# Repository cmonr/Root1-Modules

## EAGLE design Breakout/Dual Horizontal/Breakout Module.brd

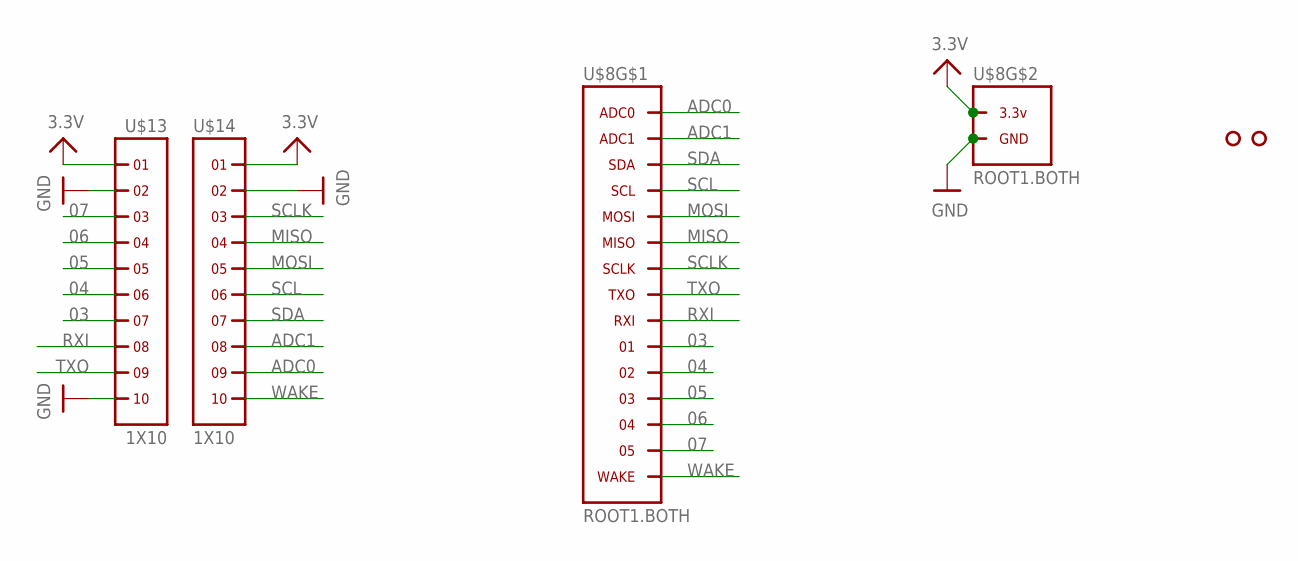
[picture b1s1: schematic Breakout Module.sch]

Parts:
U$3, U$4: HOLE.2MM; 2MM
U$8: ROOT1.BOTH
U$13, U$14: 1X10

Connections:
03: U$8.03 (01), U$8.03@1 (01), U$8.03@VIA (01), U$13.7
3.3V: U$8.3.3V@1 (3.3V), U$8.3.3V@2 (3.3V), U$8.3.3V@3 (3.3V), U$8.3.3V@4 (3.3V), U$8.3.3V@5 (3.3V), U$8.3.3V@6 (3.3V), U$8.3.3V@7 (3.3V), U$8.3.3V@8 (3.3V), U$8.3.3V@9 (3.3V), U$8.3.3V@10 (3.3V), U$8.3.3V@VIA (3.3V), U$13.1, U$14.1
04: U$8.04 (02), U$8.04@1 (02), U$8.04@VIA (02), U$13.6
05: U$8.05 (03), U$8.05@1 (03), U$8.05@VIA (03), U$13.5
06: U$8.06 (04), U$8.06@1 (04), U$8.06@VIA (04), U$13.4
07: U$8.07 (05), U$8.07@1 (05), U$8.07@VIA (05), U$13.3
ADC0: U$8.ADC0, U$8.ADC0@1 (ADC0), U$8.ADC0@VIA (ADC0), U$14.9
ADC1: U$8.ADC1, U$8.ADC1@1 (ADC1), U$8.ADC1@VIA (ADC1), U$14.8
GND: U$8.GND@1 (GND), U$8.GND@2 (GND), U$8.GND@3 (GND), U$8.GND@4 (GND), U$8.GND@5 (GND), U$8.GND@6 (GND), U$8.GND@7 (GND), U$8.GND@8 (GND), U$8.GND@9 (GND), U$8.GND@10 (GND), U$8.GND@11 (GND), U$8.GND@12 (GND), U$8.GND@13 (GND), U$8.GND@14 (GND), U$8.GND@15 (GND), U$8.GND@16 (GND), U$8.GND@17 (GND), U$8.GND@18 (GND), U$8.GND@19 (GND), U$8.GND@20 (GND), U$8.GND@VIA (GND), U$13.2, U$13.10, U$14.2
MISO: U$8.MISO, U$8.MISO@1 (MISO), U$8.MISO@VIA (MISO), U$14.4
MOSI: U$8.MOSI, U$8.MOSI@1 (MOSI), U$8.MOSI@VIA (MOSI), U$14.5
RXI: U$8.02 (RXI), U$8.02@1 (RXI), U$8.02@VIA (RXI), U$13.8
SCL: U$8.SCL, U$8.SCL@1 (SCL), U$8.SCL@VIA (SCL), U$14.6
SCLK: U$8.SCLK, U$8.SCLK@1 (SCLK), U$8.SCLK@VIA (SCLK), U$14.3
SDA: U$8.SDA, U$8.SDA@1 (SDA), U$8.SDA@VIA (SDA), U$14.7
TXO: U$8.01 (TXO), U$8.01@1 (TXO), U$8.01@VIA (TXO), U$13.9
WAKE: U$8.WAKE, U$8.WAKE@1 (WAKE), U$8.WAKE@VIA (WAKE), U$14.10

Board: 2 copper layers, 5 parts (0 on the bottom side), 17 nets, no tracks yet.

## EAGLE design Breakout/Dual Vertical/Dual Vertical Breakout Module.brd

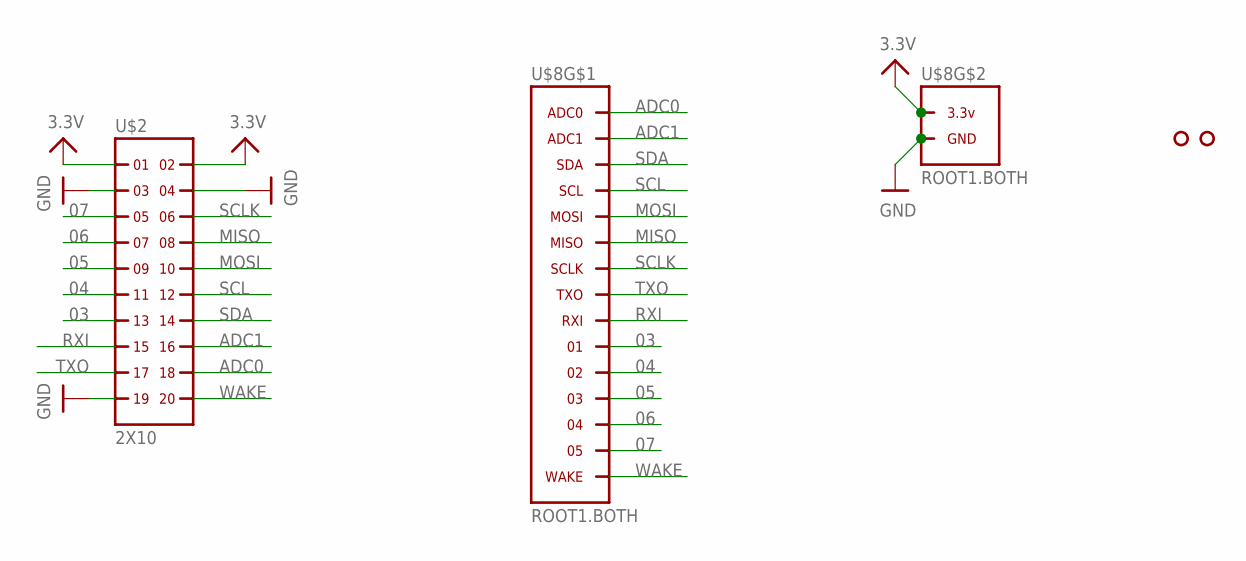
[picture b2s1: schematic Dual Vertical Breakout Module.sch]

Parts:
U$2: 2X10
U$3, U$4: HOLE.2MM; 2MM
U$8: ROOT1.BOTH

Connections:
03: U$2.13, U$8.03 (01), U$8.03@1 (01), U$8.03@VIA (01)
3.3V: U$2.1, U$2.2, U$8.3.3V@1 (3.3V), U$8.3.3V@2 (3.3V), U$8.3.3V@3 (3.3V), U$8.3.3V@4 (3.3V), U$8.3.3V@5 (3.3V), U$8.3.3V@6 (3.3V), U$8.3.3V@7 (3.3V), U$8.3.3V@8 (3.3V), U$8.3.3V@9 (3.3V), U$8.3.3V@10 (3.3V), U$8.3.3V@VIA (3.3V)
04: U$2.11, U$8.04 (02), U$8.04@1 (02), U$8.04@VIA (02)
05: U$2.9, U$8.05 (03), U$8.05@1 (03), U$8.05@VIA (03)
06: U$2.7, U$8.06 (04), U$8.06@1 (04), U$8.06@VIA (04)
07: U$2.5, U$8.07 (05), U$8.07@1 (05), U$8.07@VIA (05)
ADC0: U$2.18, U$8.ADC0, U$8.ADC0@1 (ADC0), U$8.ADC0@VIA (ADC0)
ADC1: U$2.16, U$8.ADC1, U$8.ADC1@1 (ADC1), U$8.ADC1@VIA (ADC1)
GND: U$2.3, U$2.4, U$2.19, U$8.GND@1 (GND), U$8.GND@2 (GND), U$8.GND@3 (GND), U$8.GND@4 (GND), U$8.GND@5 (GND), U$8.GND@6 (GND), U$8.GND@7 (GND), U$8.GND@8 (GND), U$8.GND@9 (GND), U$8.GND@10 (GND), U$8.GND@11 (GND), U$8.GND@12 (GND), U$8.GND@13 (GND), U$8.GND@14 (GND), U$8.GND@15 (GND), U$8.GND@16 (GND), U$8.GND@17 (GND), U$8.GND@18 (GND), U$8.GND@19 (GND), U$8.GND@20 (GND), U$8.GND@VIA (GND)
MISO: U$2.8, U$8.MISO, U$8.MISO@1 (MISO), U$8.MISO@VIA (MISO)
MOSI: U$2.10, U$8.MOSI, U$8.MOSI@1 (MOSI), U$8.MOSI@VIA (MOSI)
RXI: U$2.15, U$8.02 (RXI), U$8.02@1 (RXI), U$8.02@VIA (RXI)
SCL: U$2.12, U$8.SCL, U$8.SCL@1 (SCL), U$8.SCL@VIA (SCL)
SCLK: U$2.6, U$8.SCLK, U$8.SCLK@1 (SCLK), U$8.SCLK@VIA (SCLK)
SDA: U$2.14, U$8.SDA, U$8.SDA@1 (SDA), U$8.SDA@VIA (SDA)
TXO: U$2.17, U$8.01 (TXO), U$8.01@1 (TXO), U$8.01@VIA (TXO)
WAKE: U$2.20, U$8.WAKE, U$8.WAKE@1 (WAKE), U$8.WAKE@VIA (WAKE)

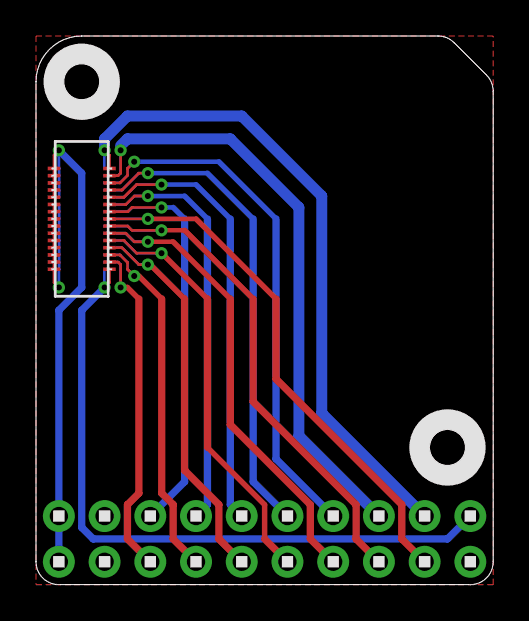
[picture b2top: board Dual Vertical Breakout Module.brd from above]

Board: 2 copper layers, 25.4 x 30.5 mm, 4 parts (0 on the bottom side), 17 nets.

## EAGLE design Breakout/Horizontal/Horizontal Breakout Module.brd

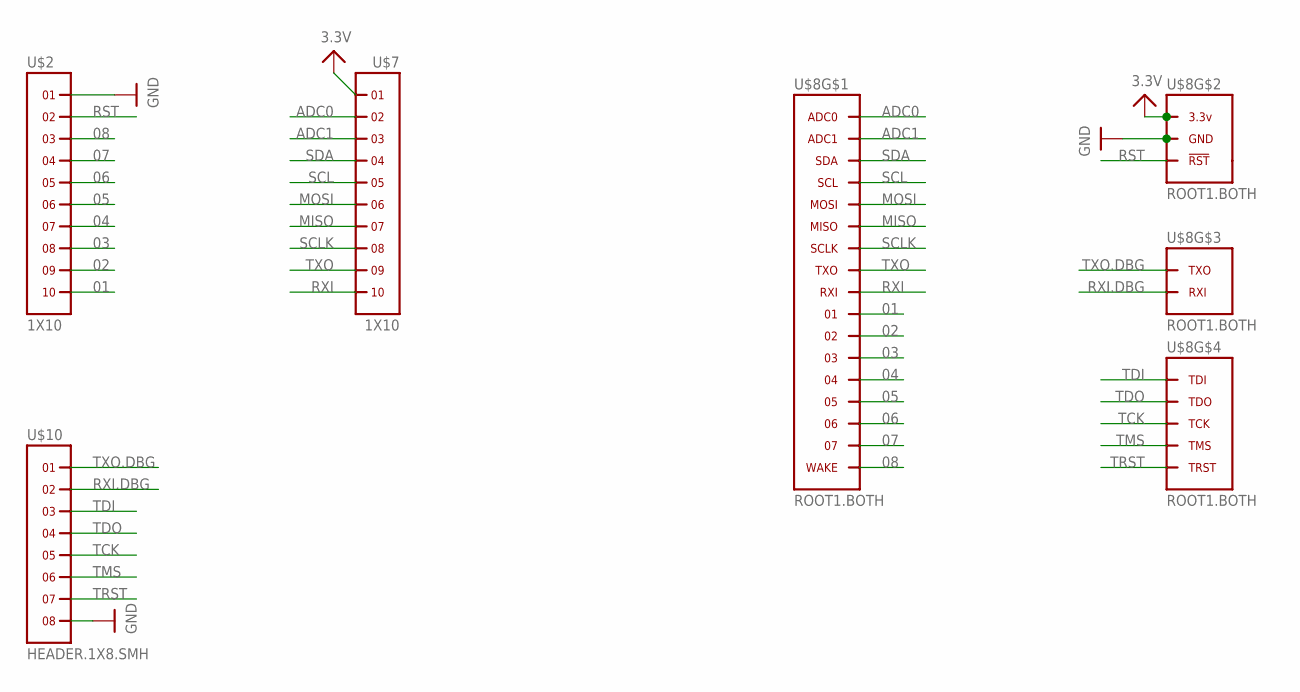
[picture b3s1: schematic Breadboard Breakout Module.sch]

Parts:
U$2, U$7: 1X10
U$8: ROOT1.BOTH
U$10: HEADER.1X8.SMH; SMH-108-XX-X-S

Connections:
01: U$2.10, U$8.01, U$8.01@1 (01), U$8.01@VIA (01)
02: U$2.9, U$8.02, U$8.02@1 (02), U$8.02@VIA (02)
03: U$2.8, U$8.03, U$8.03@1 (03), U$8.03@VIA (03)
3.3V: U$7.1, U$8.3.3V@1 (3.3V), U$8.3.3V@2 (3.3V), U$8.3.3V@3 (3.3V), U$8.3.3V@4 (3.3V), U$8.3.3V@5 (3.3V), U$8.3.3V@6 (3.3V), U$8.3.3V@7 (3.3V), U$8.3.3V@8 (3.3V), U$8.3.3V@9 (3.3V), U$8.3.3V@10 (3.3V), U$8.3.3V@11 (3.3V), U$8.3.3V@12 (3.3V), U$8.3.3V@13 (3.3V), U$8.3.3V@14 (3.3V), U$8.3.3V@15 (3.3V), U$8.3.3V@16 (3.3V), U$8.3.3V@17 (3.3V), U$8.3.3V@18 (3.3V), U$8.3.3V@19 (3.3V), U$8.3.3V@20 (3.3V), U$8.3.3V@21 (3.3V), U$8.3.3V@22 (3.3V), U$8.3.3V@23 (3.3V), U$8.3.3V@24 (3.3V), U$8.3.3V@VIA (3.3V)
04: U$2.7, U$8.04, U$8.04@1 (04), U$8.04@VIA (04)
05: U$2.6, U$8.05, U$8.05@1 (05), U$8.05@VIA (05)
06: U$2.5, U$8.06, U$8.06@1 (06), U$8.06@VIA (06)
07: U$2.4, U$8.07, U$8.07@1 (07), U$8.07@VIA (07)
08: U$2.3, U$8.WAKE, U$8.WAKE@1 (WAKE), U$8.WAKE@VIA (WAKE)
ADC0: U$7.2, U$8.ADC0, U$8.ADC0@1 (ADC0), U$8.ADC0@VIA (ADC0)
ADC1: U$7.3, U$8.ADC1, U$8.ADC1@1 (ADC1), U$8.ADC1@VIA (ADC1)
GND: U$2.1, U$8.GND@1 (GND), U$8.GND@2 (GND), U$8.GND@3 (GND), U$8.GND@4 (GND), U$8.GND@5 (GND), U$8.GND@6 (GND), U$8.GND@7 (GND), U$8.GND@8 (GND), U$8.GND@9 (GND), U$8.GND@10 (GND), U$8.GND@11 (GND), U$8.GND@12 (GND), U$8.GND@13 (GND), U$8.GND@14 (GND), U$8.GND@15 (GND), U$8.GND@16 (GND), U$8.GND@17 (GND), U$8.GND@18 (GND), U$8.GND@19 (GND), U$8.GND@20 (GND), U$8.GND@21 (GND), U$8.GND@22 (GND), U$8.GND@23 (GND), U$8.GND@24 (GND), U$8.GND@25 (GND), U$8.GND@26 (GND), U$8.GND@VIA (GND), U$10.8
MISO: U$7.7, U$8.MISO, U$8.MISO@1 (MISO), U$8.MISO@VIA (MISO)
MOSI: U$7.6, U$8.MOSI, U$8.MOSI@1 (MOSI), U$8.MOSI@VIA (MOSI)
RST: U$2.2, U$8.RST (!RST), U$8.RST@1 (!RST), U$8.RST@VIA (!RST)
RXI: U$7.10, U$8.RXI, U$8.RXI@1 (RXI), U$8.RXI@VIA (RXI)
RXI.DBG: U$8.RXI.DBG (RXI), U$8.RXI.DBG@1 (RXI), U$8.RXI.DBG@VIA (RXI), U$10.2
SCL: U$7.5, U$8.SCL, U$8.SCL@1 (SCL), U$8.SCL@VIA (SCL)
SCLK: U$7.8, U$8.SCLK, U$8.SCLK@1 (SCLK), U$8.SCLK@VIA (SCLK)
SDA: U$7.4, U$8.SDA, U$8.SDA@1 (SDA), U$8.SDA@VIA (SDA)
TCK: U$8.TCK, U$8.TCK@1 (TCK), U$8.TCK@VIA (TCK), U$10.5
TDI: U$8.TDI, U$8.TDI@1 (TDI), U$8.TDI@VIA (TDI), U$10.3
TDO: U$8.TDO, U$8.TDO@1 (TDO), U$8.TDO@VIA (TDO), U$10.4
TMS: U$8.TMS, U$8.TMS@1 (TMS), U$8.TMS@VIA (TMS), U$10.6
TRST: U$8.TRST, U$8.TRST@1 (TRST), U$8.TRST@VIA (TRST), U$10.7
TXO: U$7.9, U$8.TXO, U$8.TXO@1 (TXO), U$8.TXO@VIA (TXO)
TXO.DBG: U$8.TXO.DBG (TXO), U$8.TXO.DBG@1 (TXO), U$8.TXO.DBG@VIA (TXO), U$10.1

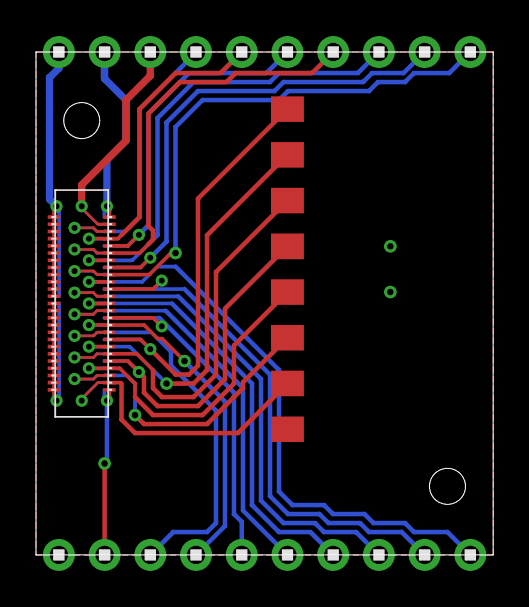
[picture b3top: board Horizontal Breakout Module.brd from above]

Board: 2 copper layers, 25.4 x 27.9 mm, 4 parts (0 on the bottom side), 27 nets.

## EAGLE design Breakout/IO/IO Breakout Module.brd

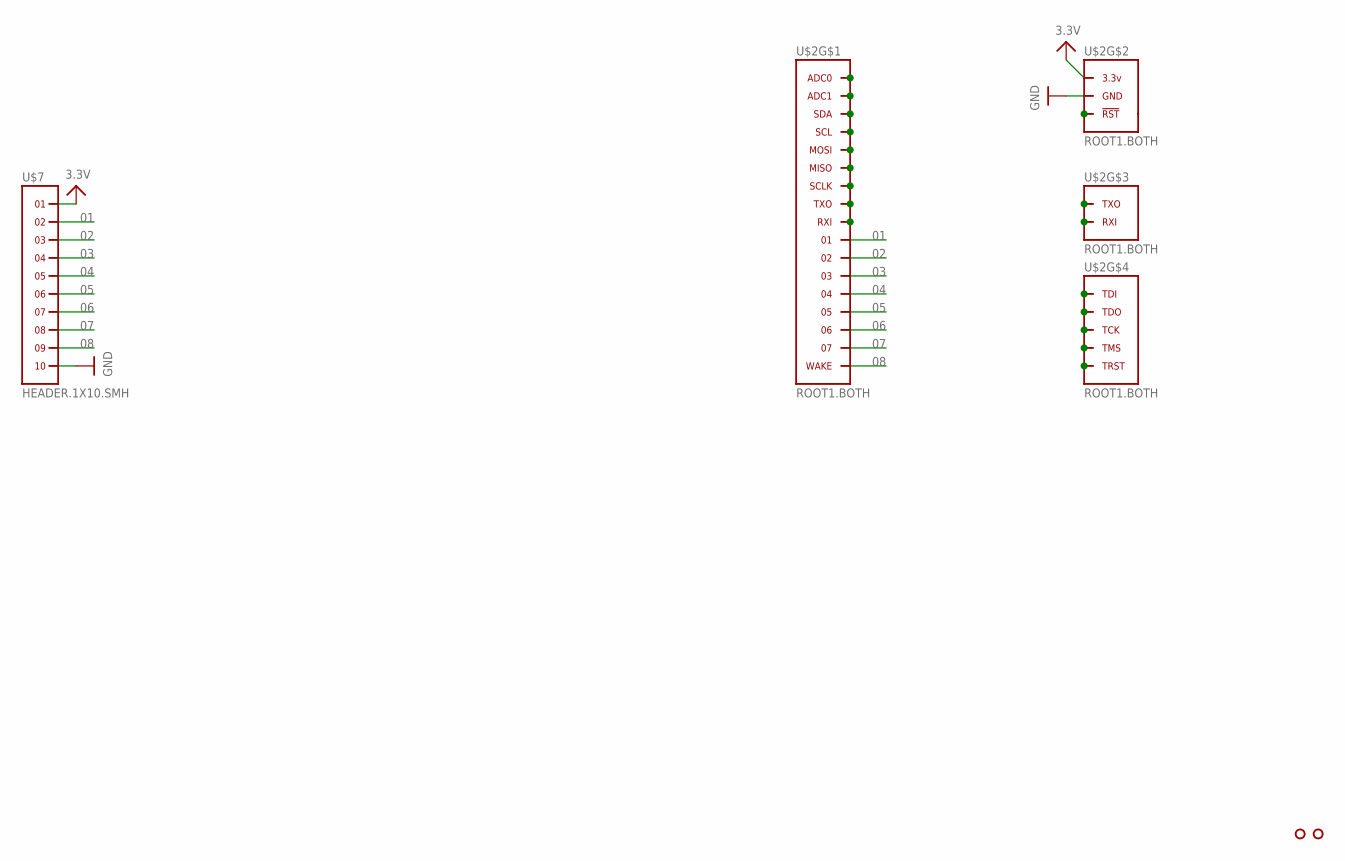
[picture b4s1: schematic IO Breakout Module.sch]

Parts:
U$2: ROOT1.BOTH
U$3, U$4: HOLE.#2; #2
U$7: HEADER.1X10.SMH; SMH-110-XX-X-S

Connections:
01: U$2.01, U$2.01@1 (01), U$2.01@VIA (01), U$7.2
02: U$2.02, U$2.02@1 (02), U$2.02@VIA (02), U$7.3
03: U$2.03, U$2.03@1 (03), U$2.03@VIA (03), U$7.4
3.3V: U$2.3.3V@1 (3.3V), U$2.3.3V@2 (3.3V), U$2.3.3V@3 (3.3V), U$2.3.3V@4 (3.3V), U$2.3.3V@5 (3.3V), U$2.3.3V@6 (3.3V), U$2.3.3V@7 (3.3V), U$2.3.3V@8 (3.3V), U$2.3.3V@9 (3.3V), U$2.3.3V@10 (3.3V), U$2.3.3V@11 (3.3V), U$2.3.3V@12 (3.3V), U$2.3.3V@13 (3.3V), U$2.3.3V@14 (3.3V), U$2.3.3V@15 (3.3V), U$2.3.3V@16 (3.3V), U$2.3.3V@17 (3.3V), U$2.3.3V@18 (3.3V), U$2.3.3V@19 (3.3V), U$2.3.3V@20 (3.3V), U$2.3.3V@21 (3.3V), U$2.3.3V@22 (3.3V), U$2.3.3V@23 (3.3V), U$2.3.3V@24 (3.3V), U$2.3.3V@VIA (3.3V), U$7.1
04: U$2.04, U$2.04@1 (04), U$2.04@VIA (04), U$7.5
05: U$2.05, U$2.05@1 (05), U$2.05@VIA (05), U$7.6
06: U$2.06, U$2.06@1 (06), U$2.06@VIA (06), U$7.7
07: U$2.07, U$2.07@1 (07), U$2.07@VIA (07), U$7.8
08: U$2.WAKE, U$2.WAKE@1 (WAKE), U$2.WAKE@VIA (WAKE), U$7.9
GND: U$2.GND@1 (GND), U$2.GND@2 (GND), U$2.GND@3 (GND), U$2.GND@4 (GND), U$2.GND@5 (GND), U$2.GND@6 (GND), U$2.GND@7 (GND), U$2.GND@8 (GND), U$2.GND@9 (GND), U$2.GND@10 (GND), U$2.GND@11 (GND), U$2.GND@12 (GND), U$2.GND@13 (GND), U$2.GND@14 (GND), U$2.GND@15 (GND), U$2.GND@16 (GND), U$2.GND@17 (GND), U$2.GND@18 (GND), U$2.GND@19 (GND), U$2.GND@20 (GND), U$2.GND@21 (GND), U$2.GND@22 (GND), U$2.GND@23 (GND), U$2.GND@24 (GND), U$2.GND@25 (GND), U$2.GND@26 (GND), U$2.GND@VIA (GND), U$7.10
unnamed: U$2.ADC1, U$2.ADC1@1 (ADC1), U$2.ADC1@VIA (ADC1)
unnamed: U$2.SDA, U$2.SDA@1 (SDA), U$2.SDA@VIA (SDA)
unnamed: U$2.SCL, U$2.SCL@1 (SCL), U$2.SCL@VIA (SCL)
unnamed: U$2.MISO, U$2.MISO@1 (MISO), U$2.MISO@VIA (MISO)
unnamed: U$2.SCLK, U$2.SCLK@1 (SCLK), U$2.SCLK@VIA (SCLK)
unnamed: U$2.TXO, U$2.TXO@1 (TXO), U$2.TXO@VIA (TXO)
unnamed: U$2.RXI, U$2.RXI@1 (RXI), U$2.RXI@VIA (RXI)
unnamed: U$2.MOSI, U$2.MOSI@1 (MOSI), U$2.MOSI@VIA (MOSI)
unnamed: U$2.ADC0, U$2.ADC0@1 (ADC0), U$2.ADC0@VIA (ADC0)
unnamed: U$2.TDI, U$2.TDI@1 (TDI), U$2.TDI@VIA (TDI)
unnamed: U$2.TDO, U$2.TDO@1 (TDO), U$2.TDO@VIA (TDO)
unnamed: U$2.TCK, U$2.TCK@1 (TCK), U$2.TCK@VIA (TCK)
unnamed: U$2.TMS, U$2.TMS@1 (TMS), U$2.TMS@VIA (TMS)
unnamed: U$2.TRST, U$2.TRST@1 (TRST), U$2.TRST@VIA (TRST)
unnamed: U$2.RXI.DBG (RXI), U$2.RXI.DBG@1 (RXI), U$2.RXI.DBG@VIA (RXI)
unnamed: U$2.TXO.DBG (TXO), U$2.TXO.DBG@1 (TXO), U$2.TXO.DBG@VIA (TXO)
unnamed: U$2.RST (!RST), U$2.RST@1 (!RST), U$2.RST@VIA (!RST)

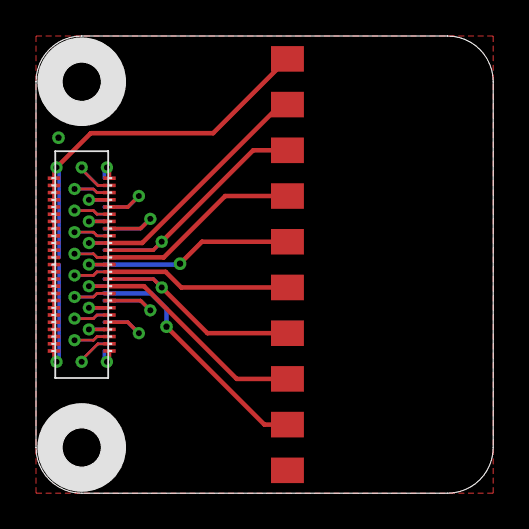
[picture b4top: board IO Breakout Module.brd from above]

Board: 2 copper layers, 25.4 x 25.4 mm, 4 parts (0 on the bottom side), 27 nets.

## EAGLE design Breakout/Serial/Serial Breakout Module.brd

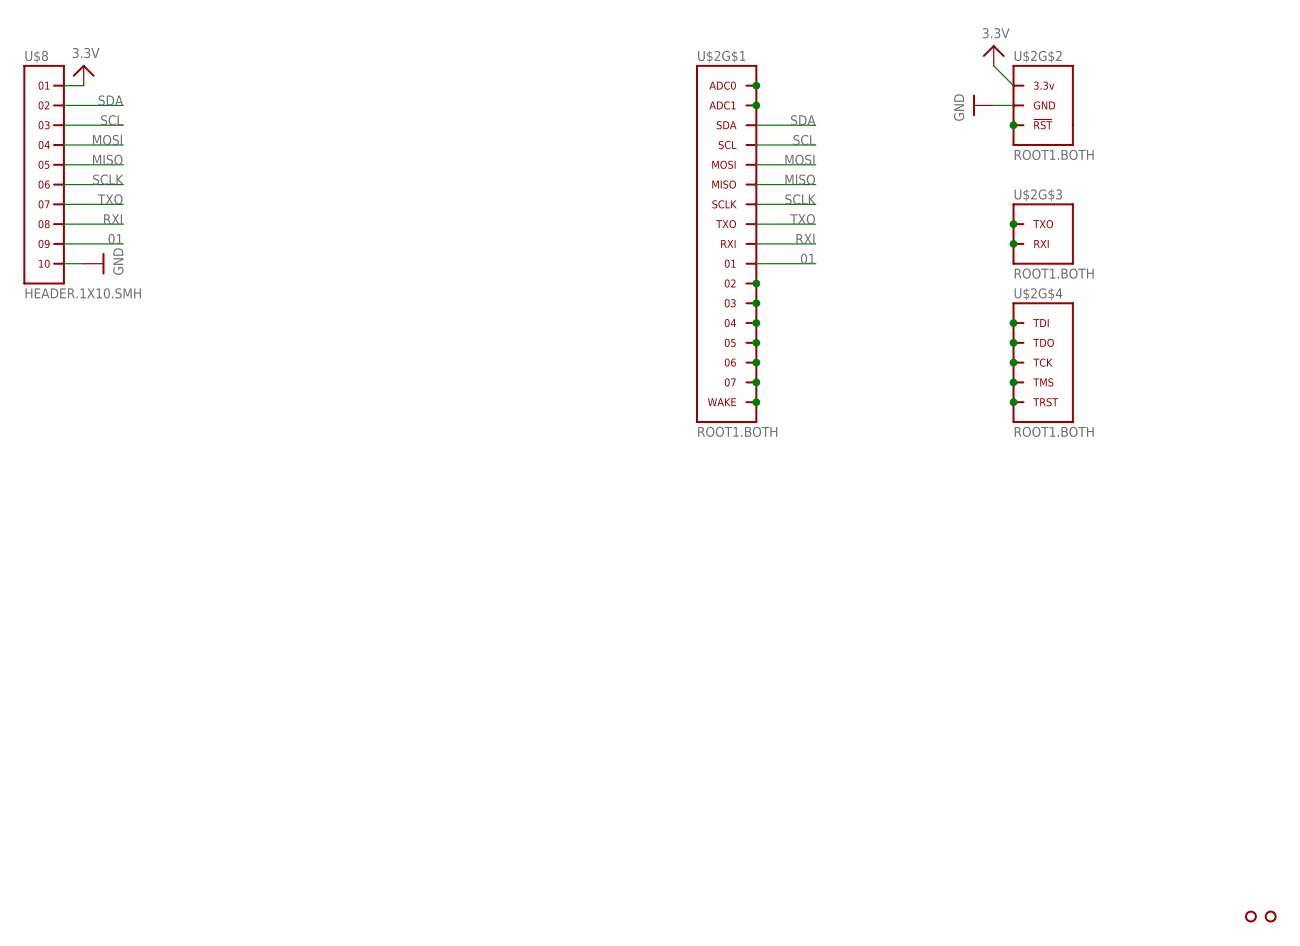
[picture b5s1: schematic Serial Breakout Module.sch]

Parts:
U$2: ROOT1.BOTH
U$3, U$4: HOLE.#2; #2
U$8: HEADER.1X10.SMH; SMH-110-XX-X-S

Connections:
01: U$2.01, U$2.01@1 (01), U$2.01@VIA (01), U$8.9
3.3V: U$2.3.3V@1 (3.3V), U$2.3.3V@2 (3.3V), U$2.3.3V@3 (3.3V), U$2.3.3V@4 (3.3V), U$2.3.3V@5 (3.3V), U$2.3.3V@6 (3.3V), U$2.3.3V@7 (3.3V), U$2.3.3V@8 (3.3V), U$2.3.3V@9 (3.3V), U$2.3.3V@10 (3.3V), U$2.3.3V@11 (3.3V), U$2.3.3V@12 (3.3V), U$2.3.3V@13 (3.3V), U$2.3.3V@14 (3.3V), U$2.3.3V@15 (3.3V), U$2.3.3V@16 (3.3V), U$2.3.3V@17 (3.3V), U$2.3.3V@18 (3.3V), U$2.3.3V@19 (3.3V), U$2.3.3V@20 (3.3V), U$2.3.3V@21 (3.3V), U$2.3.3V@22 (3.3V), U$2.3.3V@23 (3.3V), U$2.3.3V@24 (3.3V), U$2.3.3V@VIA (3.3V), U$8.1
GND: U$2.GND@1 (GND), U$2.GND@2 (GND), U$2.GND@3 (GND), U$2.GND@4 (GND), U$2.GND@5 (GND), U$2.GND@6 (GND), U$2.GND@7 (GND), U$2.GND@8 (GND), U$2.GND@9 (GND), U$2.GND@10 (GND), U$2.GND@11 (GND), U$2.GND@12 (GND), U$2.GND@13 (GND), U$2.GND@14 (GND), U$2.GND@15 (GND), U$2.GND@16 (GND), U$2.GND@17 (GND), U$2.GND@18 (GND), U$2.GND@19 (GND), U$2.GND@20 (GND), U$2.GND@21 (GND), U$2.GND@22 (GND), U$2.GND@23 (GND), U$2.GND@24 (GND), U$2.GND@25 (GND), U$2.GND@26 (GND), U$2.GND@VIA (GND), U$8.10
MISO: U$2.MISO, U$2.MISO@1 (MISO), U$2.MISO@VIA (MISO), U$8.5
MOSI: U$2.MOSI, U$2.MOSI@1 (MOSI), U$2.MOSI@VIA (MOSI), U$8.4
unnamed: U$2.04, U$2.04@1 (04), U$2.04@VIA (04)
unnamed: U$2.ADC1, U$2.ADC1@1 (ADC1), U$2.ADC1@VIA (ADC1)
unnamed: U$2.03, U$2.03@1 (03), U$2.03@VIA (03)
unnamed: U$2.02, U$2.02@1 (02), U$2.02@VIA (02)
unnamed: U$2.ADC0, U$2.ADC0@1 (ADC0), U$2.ADC0@VIA (ADC0)
unnamed: U$2.05, U$2.05@1 (05), U$2.05@VIA (05)
unnamed: U$2.06, U$2.06@1 (06), U$2.06@VIA (06)
unnamed: U$2.07, U$2.07@1 (07), U$2.07@VIA (07)
unnamed: U$2.WAKE, U$2.WAKE@1 (WAKE), U$2.WAKE@VIA (WAKE)
unnamed: U$2.TDI, U$2.TDI@1 (TDI), U$2.TDI@VIA (TDI)
unnamed: U$2.TDO, U$2.TDO@1 (TDO), U$2.TDO@VIA (TDO)
unnamed: U$2.TCK, U$2.TCK@1 (TCK), U$2.TCK@VIA (TCK)
unnamed: U$2.TMS, U$2.TMS@1 (TMS), U$2.TMS@VIA (TMS)
unnamed: U$2.TRST, U$2.TRST@1 (TRST), U$2.TRST@VIA (TRST)
unnamed: U$2.RXI.DBG (RXI), U$2.RXI.DBG@1 (RXI), U$2.RXI.DBG@VIA (RXI)
unnamed: U$2.TXO.DBG (TXO), U$2.TXO.DBG@1 (TXO), U$2.TXO.DBG@VIA (TXO)
unnamed: U$2.RST (!RST), U$2.RST@1 (!RST), U$2.RST@VIA (!RST)
RXI: U$2.RXI, U$2.RXI@1 (RXI), U$2.RXI@VIA (RXI), U$8.8
SCL: U$2.SCL, U$2.SCL@1 (SCL), U$2.SCL@VIA (SCL), U$8.3
SCLK: U$2.SCLK, U$2.SCLK@1 (SCLK), U$2.SCLK@VIA (SCLK), U$8.6
SDA: U$2.SDA, U$2.SDA@1 (SDA), U$2.SDA@VIA (SDA), U$8.2
TXO: U$2.TXO, U$2.TXO@1 (TXO), U$2.TXO@VIA (TXO), U$8.7

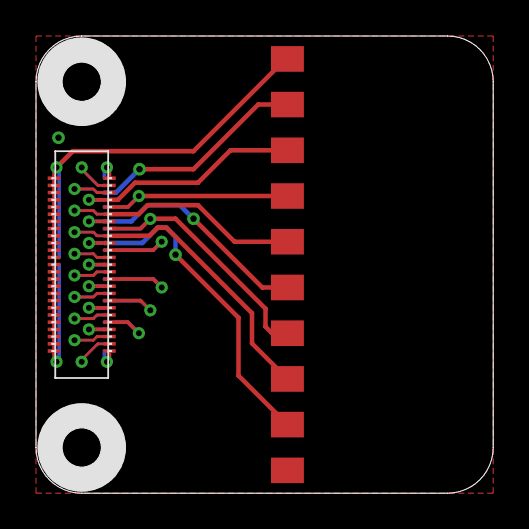
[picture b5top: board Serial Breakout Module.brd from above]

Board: 2 copper layers, 25.4 x 25.4 mm, 4 parts (0 on the bottom side), 27 nets.

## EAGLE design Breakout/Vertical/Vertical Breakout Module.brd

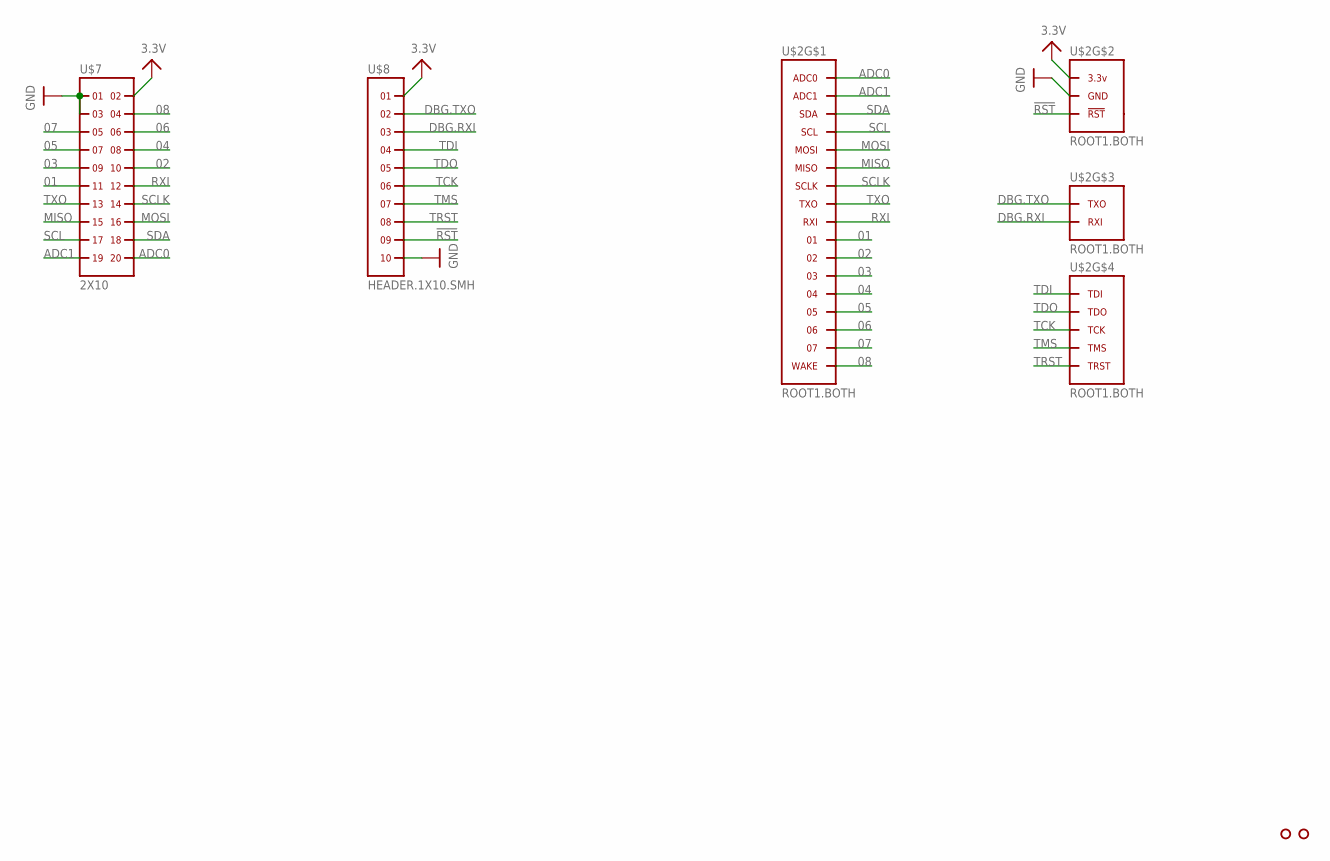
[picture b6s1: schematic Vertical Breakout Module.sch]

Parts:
U$2: ROOT1.BOTH
U$3, U$4: HOLE.#2; #2
U$7: 2X10
U$8: HEADER.1X10.SMH; SMH-110-XX-X-S

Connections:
01: U$2.01, U$2.01@1 (01), U$2.01@VIA (01), U$7.11
02: U$2.02, U$2.02@1 (02), U$2.02@VIA (02), U$7.10
03: U$2.03, U$2.03@1 (03), U$2.03@VIA (03), U$7.9
3.3V: U$2.3.3V@1 (3.3V), U$2.3.3V@2 (3.3V), U$2.3.3V@3 (3.3V), U$2.3.3V@4 (3.3V), U$2.3.3V@5 (3.3V), U$2.3.3V@6 (3.3V), U$2.3.3V@7 (3.3V), U$2.3.3V@8 (3.3V), U$2.3.3V@9 (3.3V), U$2.3.3V@10 (3.3V), U$2.3.3V@11 (3.3V), U$2.3.3V@12 (3.3V), U$2.3.3V@13 (3.3V), U$2.3.3V@14 (3.3V), U$2.3.3V@15 (3.3V), U$2.3.3V@16 (3.3V), U$2.3.3V@17 (3.3V), U$2.3.3V@18 (3.3V), U$2.3.3V@19 (3.3V), U$2.3.3V@20 (3.3V), U$2.3.3V@21 (3.3V), U$2.3.3V@22 (3.3V), U$2.3.3V@23 (3.3V), U$2.3.3V@24 (3.3V), U$2.3.3V@VIA (3.3V), U$7.2, U$8.1
04: U$2.04, U$2.04@1 (04), U$2.04@VIA (04), U$7.8
05: U$2.05, U$2.05@1 (05), U$2.05@VIA (05), U$7.7
06: U$2.06, U$2.06@1 (06), U$2.06@VIA (06), U$7.6
07: U$2.07, U$2.07@1 (07), U$2.07@VIA (07), U$7.5
08: U$2.WAKE, U$2.WAKE@1 (WAKE), U$2.WAKE@VIA (WAKE), U$7.4
!RST: U$2.RST (!RST), U$2.RST@1 (!RST), U$2.RST@VIA (!RST), U$8.9
ADC0: U$2.ADC0, U$2.ADC0@1 (ADC0), U$2.ADC0@VIA (ADC0), U$7.20
ADC1: U$2.ADC1, U$2.ADC1@1 (ADC1), U$2.ADC1@VIA (ADC1), U$7.19
DBG.RXI: U$2.RXI.DBG (RXI), U$2.RXI.DBG@1 (RXI), U$2.RXI.DBG@VIA (RXI), U$8.3
DBG.TXO: U$2.TXO.DBG (TXO), U$2.TXO.DBG@1 (TXO), U$2.TXO.DBG@VIA (TXO), U$8.2
GND: U$2.GND@1 (GND), U$2.GND@2 (GND), U$2.GND@3 (GND), U$2.GND@4 (GND), U$2.GND@5 (GND), U$2.GND@6 (GND), U$2.GND@7 (GND), U$2.GND@8 (GND), U$2.GND@9 (GND), U$2.GND@10 (GND), U$2.GND@11 (GND), U$2.GND@12 (GND), U$2.GND@13 (GND), U$2.GND@14 (GND), U$2.GND@15 (GND), U$2.GND@16 (GND), U$2.GND@17 (GND), U$2.GND@18 (GND), U$2.GND@19 (GND), U$2.GND@20 (GND), U$2.GND@21 (GND), U$2.GND@22 (GND), U$2.GND@23 (GND), U$2.GND@24 (GND), U$2.GND@25 (GND), U$2.GND@26 (GND), U$2.GND@VIA (GND), U$7.1, U$7.3, U$8.10
MISO: U$2.MISO, U$2.MISO@1 (MISO), U$2.MISO@VIA (MISO), U$7.15
MOSI: U$2.MOSI, U$2.MOSI@1 (MOSI), U$2.MOSI@VIA (MOSI), U$7.16
RXI: U$2.RXI, U$2.RXI@1 (RXI), U$2.RXI@VIA (RXI), U$7.12
SCL: U$2.SCL, U$2.SCL@1 (SCL), U$2.SCL@VIA (SCL), U$7.17
SCLK: U$2.SCLK, U$2.SCLK@1 (SCLK), U$2.SCLK@VIA (SCLK), U$7.14
SDA: U$2.SDA, U$2.SDA@1 (SDA), U$2.SDA@VIA (SDA), U$7.18
TCK: U$2.TCK, U$2.TCK@1 (TCK), U$2.TCK@VIA (TCK), U$8.6
TDI: U$2.TDI, U$2.TDI@1 (TDI), U$2.TDI@VIA (TDI), U$8.4
TDO: U$2.TDO, U$2.TDO@1 (TDO), U$2.TDO@VIA (TDO), U$8.5
TMS: U$2.TMS, U$2.TMS@1 (TMS), U$2.TMS@VIA (TMS), U$8.7
TRST: U$2.TRST, U$2.TRST@1 (TRST), U$2.TRST@VIA (TRST), U$8.8
TXO: U$2.TXO, U$2.TXO@1 (TXO), U$2.TXO@VIA (TXO), U$7.13

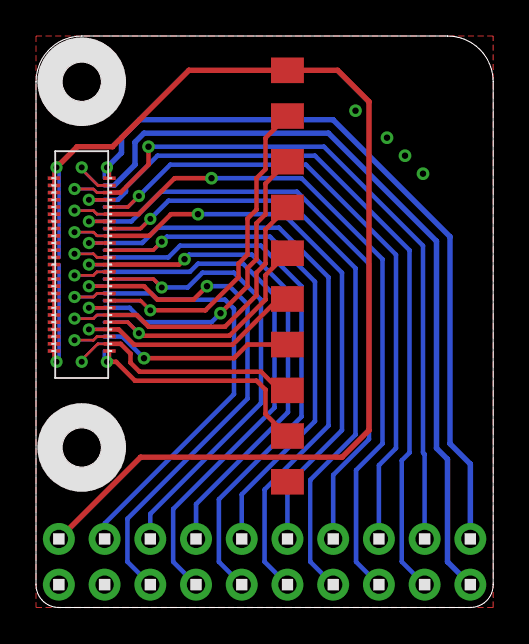
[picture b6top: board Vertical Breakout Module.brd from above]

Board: 2 copper layers, 25.4 x 31.8 mm, 5 parts (0 on the bottom side), 27 nets.

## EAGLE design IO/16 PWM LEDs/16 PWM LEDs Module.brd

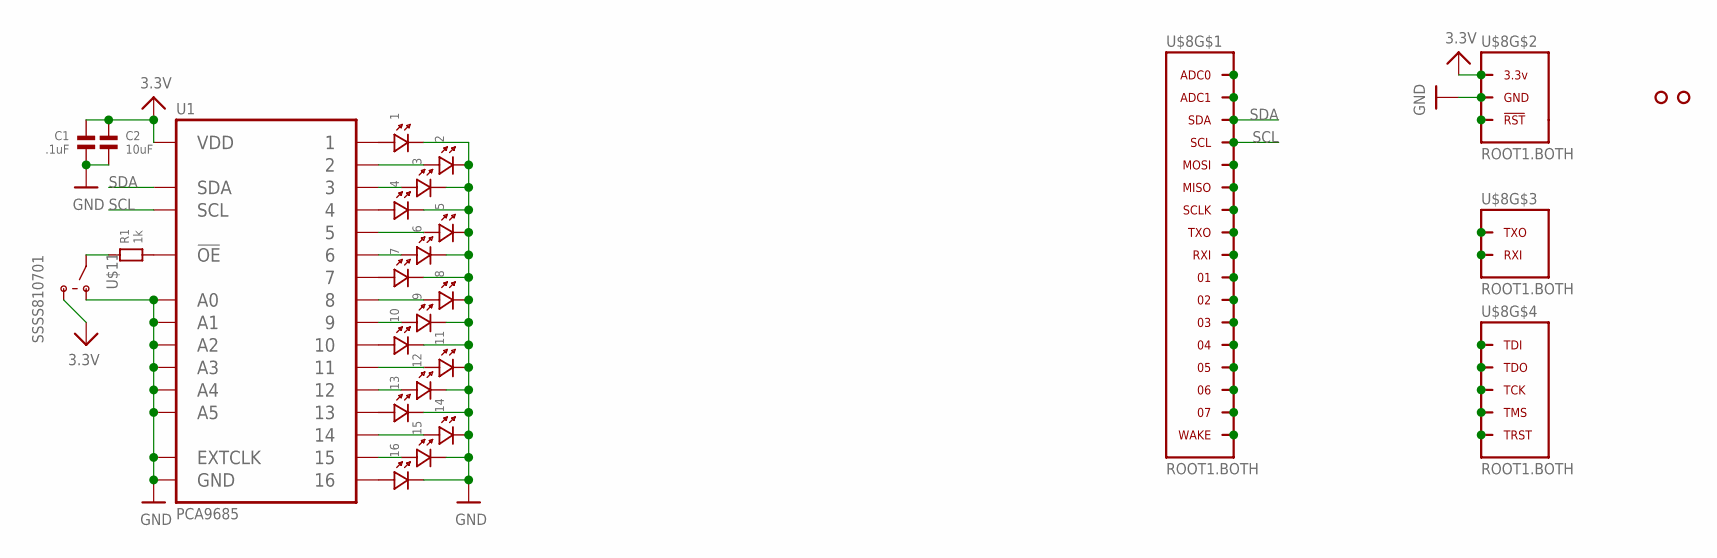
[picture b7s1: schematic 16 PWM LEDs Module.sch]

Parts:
1, 2, 3, 4, 5, 6, 7, 8, 9, 10, 11, 12, 13, 14, 15, 16: LED.0603; 0603.LED
C1: .1uF; 0603
C2: 10uF; 0805
R1: 1k; 0603
U1: PCA9685; HVQFN28
U$3, U$4: HOLE.2MM; 2MM
U$8: ROOT1.BOTH
U$11: SSSS810701

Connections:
3.3V: C1.1, C2.1, U1.28 (VDD), U$8.3.3V@1 (3.3V), U$8.3.3V@2 (3.3V), U$8.3.3V@3 (3.3V), U$8.3.3V@4 (3.3V), U$8.3.3V@5 (3.3V), U$8.3.3V@6 (3.3V), U$8.3.3V@7 (3.3V), U$8.3.3V@8 (3.3V), U$8.3.3V@9 (3.3V), U$8.3.3V@10 (3.3V), U$8.3.3V@11 (3.3V), U$8.3.3V@12 (3.3V), U$8.3.3V@13 (3.3V), U$8.3.3V@14 (3.3V), U$8.3.3V@15 (3.3V), U$8.3.3V@16 (3.3V), U$8.3.3V@17 (3.3V), U$8.3.3V@18 (3.3V), U$8.3.3V@19 (3.3V), U$8.3.3V@20 (3.3V), U$8.3.3V@21 (3.3V), U$8.3.3V@22 (3.3V), U$8.3.3V@23 (3.3V), U$8.3.3V@24 (3.3V), U$8.3.3V@VIA (3.3V), U$11.1 (B)
GND: 1.P$2 (2), 2.P$2 (2), 3.P$2 (2), 4.P$2 (2), 5.P$2 (2), 6.P$2 (2), 7.P$2 (2), 8.P$2 (2), 9.P$2 (2), 10.P$2 (2), 11.P$2 (2), 12.P$2 (2), 13.P$2 (2), 14.P$2 (2), 15.P$2 (2), 16.P$2 (2), C1.2, C2.2, U1.1 (A0), U1.2 (A1), U1.3 (A2), U1.4 (A3), U1.5 (A4), U1.14 (GND), U1.24 (A5), U1.25 (EXTCLK), U1.PAD (GND), U$8.GND@1 (GND), U$8.GND@2 (GND), U$8.GND@3 (GND), U$8.GND@4 (GND), U$8.GND@5 (GND), U$8.GND@6 (GND), U$8.GND@7 (GND), U$8.GND@8 (GND), U$8.GND@9 (GND), U$8.GND@10 (GND), U$8.GND@11 (GND), U$8.GND@12 (GND), U$8.GND@13 (GND), U$8.GND@14 (GND), U$8.GND@15 (GND), U$8.GND@16 (GND), U$8.GND@17 (GND), U$8.GND@18 (GND), U$8.GND@19 (GND), U$8.GND@20 (GND), U$8.GND@21 (GND), U$8.GND@22 (GND), U$8.GND@23 (GND), U$8.GND@24 (GND), U$8.GND@25 (GND), U$8.GND@26 (GND), U$8.GND@VIA (GND), U$11.3 (A)
unnamed: U$8.ADC0, U$8.ADC0@1 (ADC0), U$8.ADC0@VIA (ADC0)
unnamed: U$8.ADC1, U$8.ADC1@1 (ADC1), U$8.ADC1@VIA (ADC1)
unnamed: R1.2, U1.23 (!OE)
unnamed: R1.1, U$11.2 (COM)
unnamed: U$8.MOSI, U$8.MOSI@1 (MOSI), U$8.MOSI@VIA (MOSI)
unnamed: U$8.MISO, U$8.MISO@1 (MISO), U$8.MISO@VIA (MISO)
unnamed: U$8.SCLK, U$8.SCLK@1 (SCLK), U$8.SCLK@VIA (SCLK)
unnamed: U$8.TXO, U$8.TXO@1 (TXO), U$8.TXO@VIA (TXO)
unnamed: U$8.RXI, U$8.RXI@1 (RXI), U$8.RXI@VIA (RXI)
unnamed: U$8.01, U$8.01@1 (01), U$8.01@VIA (01)
unnamed: U$8.02, U$8.02@1 (02), U$8.02@VIA (02)
unnamed: U$8.03, U$8.03@1 (03), U$8.03@VIA (03)
unnamed: U$8.04, U$8.04@1 (04), U$8.04@VIA (04)
unnamed: U$8.05, U$8.05@1 (05), U$8.05@VIA (05)
unnamed: U$8.WAKE, U$8.WAKE@1 (WAKE), U$8.WAKE@VIA (WAKE)
unnamed: 1.P$1 (1), U1.6 (1)
unnamed: 2.P$1 (1), U1.7 (2)
unnamed: 3.P$1 (1), U1.8 (3)
unnamed: 4.P$1 (1), U1.9 (4)
unnamed: 5.P$1 (1), U1.10 (5)
unnamed: 6.P$1 (1), U1.11 (6)
unnamed: 7.P$1 (1), U1.12 (7)
unnamed: 8.P$1 (1), U1.13 (8)
unnamed: 9.P$1 (1), U1.15 (9)
unnamed: 10.P$1 (1), U1.16 (10)
unnamed: 11.P$1 (1), U1.17 (11)
unnamed: 12.P$1 (1), U1.18 (12)
unnamed: 13.P$1 (1), U1.19 (13)
unnamed: 14.P$1 (1), U1.20 (14)
unnamed: 15.P$1 (1), U1.21 (15)
unnamed: 16.P$1 (1), U1.22 (16)
unnamed: U$8.TXO.DBG (TXO), U$8.TXO.DBG@1 (TXO), U$8.TXO.DBG@VIA (TXO)
unnamed: U$8.RST (!RST), U$8.RST@1 (!RST), U$8.RST@VIA (!RST)
unnamed: U$8.RXI.DBG (RXI), U$8.RXI.DBG@1 (RXI), U$8.RXI.DBG@VIA (RXI)
unnamed: U$8.TDI, U$8.TDI@1 (TDI), U$8.TDI@VIA (TDI)
unnamed: U$8.07, U$8.07@1 (07), U$8.07@VIA (07)
unnamed: U$8.06, U$8.06@1 (06), U$8.06@VIA (06)
unnamed: U$8.TDO, U$8.TDO@1 (TDO), U$8.TDO@VIA (TDO)
unnamed: U$8.TCK, U$8.TCK@1 (TCK), U$8.TCK@VIA (TCK)
unnamed: U$8.TMS, U$8.TMS@1 (TMS), U$8.TMS@VIA (TMS)
unnamed: U$8.TRST, U$8.TRST@1 (TRST), U$8.TRST@VIA (TRST)
SCL: U1.26 (SCL), U$8.SCL, U$8.SCL@1 (SCL), U$8.SCL@VIA (SCL)
SDA: U1.27 (SDA), U$8.SDA, U$8.SDA@1 (SDA), U$8.SDA@VIA (SDA)

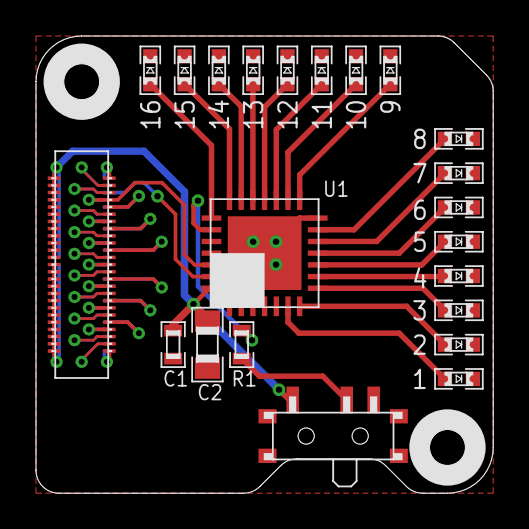
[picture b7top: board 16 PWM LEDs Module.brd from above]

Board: 2 copper layers, 25.4 x 25.4 mm, 24 parts (0 on the bottom side), 45 nets.
